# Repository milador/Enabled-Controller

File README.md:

# Enabled Controller

Enabled Controller Wireless is an open-source switch interface that enables those with limited or no hand movement to be able to use Adaptive switches and analog joysticks as inputs to operate their computers, smartphones, and game consoles.

The device offers up to eight switch input enclosures through eight 3.5mm audio jacks and four analog inputs through two 3.5mm headphone jacks. The two 3.5mm headphone jacks can be used to connect up to two X-Y analog joysticks.

The internal RGB led of ItsyBitsy and external NeoPixel is used to provide visual feedback for each action.

## Assembly Instructions Manual

The <a href="https://github.com/milador/Enabled-Controller/blob/master/Documentation/Build_Manuals/Enabled_Controller_Instructions_Manual.pdf">Assembly Instructions Manual</a> is available to download.

## User Manual

### Enabled Controller USB User Manual

<a href="https://github.com/milador/Enabled-Controller/blob/master/Documentation/User_Manuals/Enabled_Controller_USB_User_Manual.pdf">Enabled_Controller_USB_User_Manual.pdf</a>

### Enabled Controller Joystick User Manual 

<a href="https://github.com/milador/Enabled-Controller/blob/master/Documentation/User_Manuals/Enabled_Controller_Joystick_User_Manual.pdf">Enabled_Controller_Joystick_User_Manual.pdf</a>

## Parts

The <a href="https://github.com/milador/Enabled-Controller/blob/master/Components/Enabled_Controller_BOM.csv">BOM</a> file is available to download.

## Software

### Enabled_Controller_USB_Software.ino  

The <a href="https://raw.githubusercontent.com/milador/Enabled-Controller/master/Software/Arduino/Enabled_Controller_USB_Software/Enabled_Controller_USB_Software.ino">Enabled_Controller_USB_Software.ino</a> allows you to use adaptive switches as input method via keyboard/mouse HID profiles. 

### Enabled_Controller_Joystick_Software.ino  

The <a href="https://raw.githubusercontent.com/milador/Enabled-Controller/master/Software/Arduino/Enabled_Controller_Joystick_Software/Enabled_Controller_Joystick_Software.ino">Enabled_Controller_Joystick_Software.ino</a> allows you to use adaptive switches as input method via joystick HID profiles. 

## Hardware 

### PCB Design 

The <a href="https://github.com/milador/Enabled-Controller/tree/master/Hardware/PCB">PCB files</a> including both PCB Eagle design files and generated gerber files are available to download.

Front PCB:

Back PCB:

Assembled:

Assembly Animation:

https://www.youtube.com/watch?v=7AMCL-cITrQ

### Enclosure

The <a href="https://github.com/milador/Enabled-Controller/tree/master/Hardware/Enclosure">Enclosure files</a> including both STL and STEP enclosure files are available to download.

## License

### Creative Commons Attribution-NonCommercial-ShareAlike (CC-BY-NC-SA)

Copyright (c) 2020 Milador

A creative commons license that bans commercial use and requires you to release any modified works under this license.

<br />This work is licensed under a <a rel="license" href="http://creativecommons.org/licenses/by-nc-sa/3.0/">Creative Commons Attribution-NonCommercial-ShareAlike 3.0 Unported License</a>.

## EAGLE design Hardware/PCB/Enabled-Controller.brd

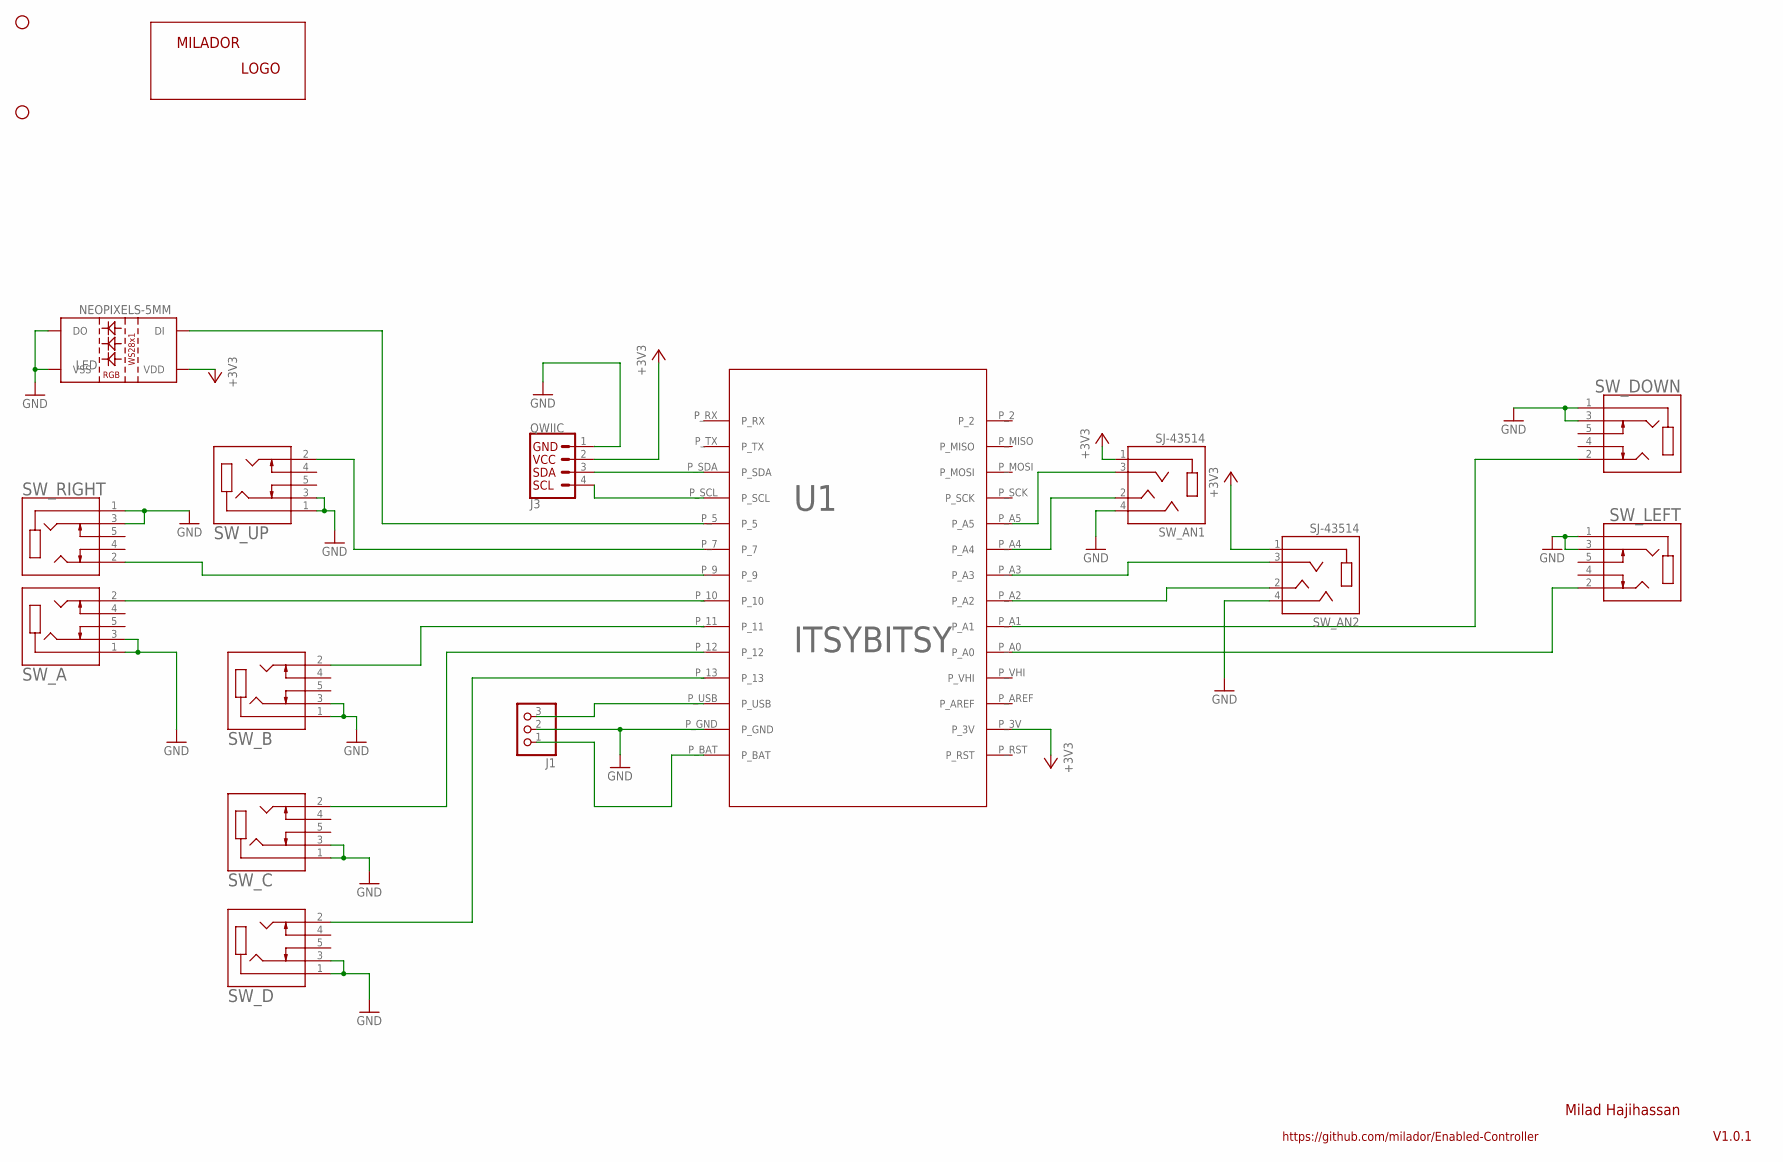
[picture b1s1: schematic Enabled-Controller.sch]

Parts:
J1: HEADER_FEMALE-1X3-LONGER; HEADER_FEMALE-1X03_LONGER
J3: QWIIC; CONNECTORS_JST04_1MM_RA
LABEL1: MILADOR-LOGO-; MILADOR_LOGO1
LED: NEOPIXELS-5MM
STANDOFF1, STANDOFF2: STAND-OFF-; STAND-OFF
SW_A: CUI_SJ1-3535NGSJ1-3535NG; CUI_SJ1-3535NG
SW_AN1, SW_AN2: SJ-43514; CUI_SJ-43514
SW_B: CUI_SJ1-3535NGSJ1-3535NG; CUI_SJ1-3535NG
SW_C: CUI_SJ1-3535NGSJ1-3535NG; CUI_SJ1-3535NG
SW_D: CUI_SJ1-3535NGSJ1-3535NG; CUI_SJ1-3535NG
SW_DOWN: CUI_SJ1-3535NGSJ1-3535NG; CUI_SJ1-3535NG
SW_LEFT: CUI_SJ1-3535NGSJ1-3535NG; CUI_SJ1-3535NG
SW_RIGHT: CUI_SJ1-3535NGSJ1-3535NG; CUI_SJ1-3535NG
SW_UP: CUI_SJ1-3535NGSJ1-3535NG; CUI_SJ1-3535NG
U1: ITSYBITSY; ITSYBITSY-V2

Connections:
+3V3: J3.2, LED.P2 (VDD), SW_AN1.1 (SLEEVE), SW_AN2.1 (SLEEVE), U1.P_3V
GND: J1.2, J3.1, LED.P3 (VSS), LED.P4 (DO), SW_A.1, SW_A.3, SW_AN1.4 (RING2), SW_AN2.4 (RING2), SW_B.1, SW_B.3, SW_C.1, SW_C.3, SW_D.1, SW_D.3, SW_DOWN.1, SW_DOWN.3, SW_LEFT.1, SW_LEFT.3, SW_RIGHT.1, SW_RIGHT.3, SW_UP.1, SW_UP.3, U1.P_GND
unnamed: SW_D.2, U1.P_13
unnamed: SW_C.2, U1.P_12
unnamed: SW_B.2, U1.P_11
unnamed: SW_AN1.2 (TIP), U1.P_A4
unnamed: SW_DOWN.2, U1.P_A1
unnamed: SW_RIGHT.2, U1.P_9
unnamed: SW_UP.2, U1.P_7
unnamed: SW_AN1.3 (RING1), U1.P_A5
unnamed: SW_AN2.3 (RING1), U1.P_A3
unnamed: SW_A.2, U1.P_10
unnamed: SW_LEFT.2, U1.P_A0
unnamed: SW_AN2.2 (TIP), U1.P_A2
unnamed: LED.P1 (DI), U1.P_5
unnamed: J3.4, U1.P_SCL
unnamed: J3.3, U1.P_SDA
unnamed: J1.3, U1.P_USB
unnamed: J1.1, U1.P_BAT

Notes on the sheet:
V1.0.1
Milad Hajihassan
https://github.com/milador/Enabled-Controller

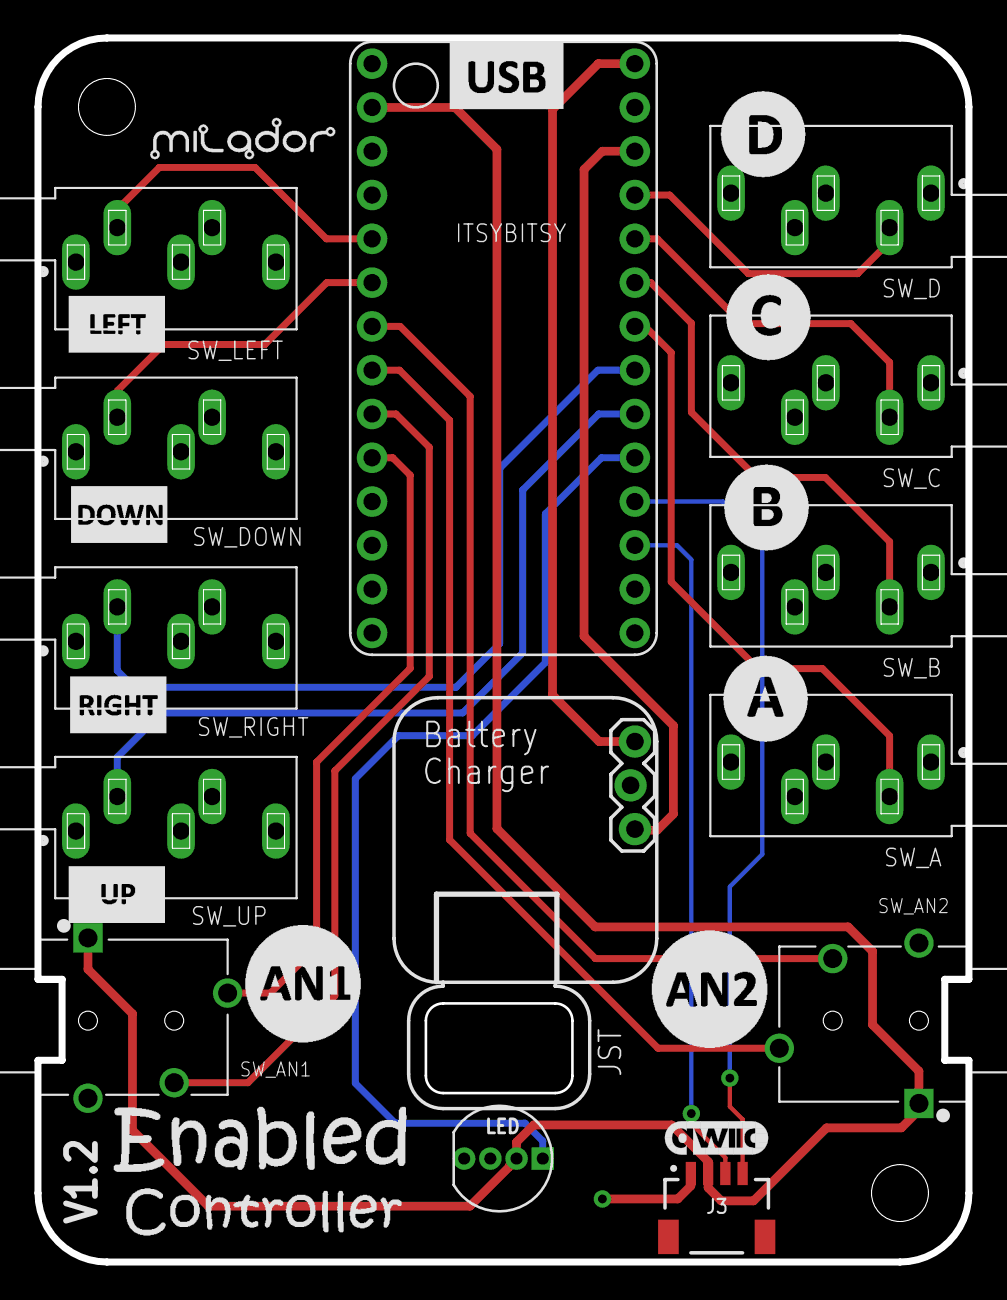
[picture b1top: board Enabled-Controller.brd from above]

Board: 2 copper layers, 54.0 x 71.0 mm, 18 parts (0 on the bottom side), 19 nets.

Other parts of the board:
LABEL2: QWIIC_6MM

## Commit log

2020-10-01 Added components list
2020-10-01 Added PCB files
2020-10-01 Added experimental software
2020-10-01 Added pictures
2020-10-01 Updated readme file
2020-11-29 Added enclosure files
2020-11-29 Updated Enclosure files for easy print
2020-12-20 Updated BOM and added M2.5 screws
2020-12-20 Redesigned the enclosure ( Snap fit )
2020-12-23 Updated BOM for two versions
2020-12-23 Added Instructions manual version 1.0
2020-12-23 Updated software naming convention
2020-12-26 Updated manual
2020-12-26 Updated the USB Software
2020-12-26 Waiting for Joystick API
2020-12-26 Waiting for BT joystick API
2021-01-12 Updated enclosure files
2021-01-17 Updated Enclosure : Snap wall height was increased by 0.8mm.
2021-01-18 Updated BOM file : Price updated and changed screw part
2021-01-18 Added the Assembly Instructions Manual
2021-01-18 Added PCB gerber files
2021-01-18 Updated Images
2021-01-18 Moved the arduino code to new directory
2021-01-18 Updated the manual : Updated software link
2021-01-18 Updated information
2021-01-18 Updated readme : Corrected links
2021-01-21 USB Switch and joystick code added
2021-01-21 Updated Software : Fixed LED code and added more switch options
2021-01-21 Updated instructions
2021-01-21 Updated user manual title
2021-01-21 Added user manuals
2021-01-21 Added software and user manual links to readme
2021-01-25 Added Joystick Assembly
2021-01-25 Updated tables and instructions based on software change ( e,f,g,h keys to UP, RIGHT, DOWN,LEFT Keys)
2021-01-25 Updated switch key codes and added OS Profile selection option ( e,f,g,h keys to UP, RIGHT, DOWN,LEFT Keys)
2021-01-31 Updated Assembly manual 1.11
2021-02-01 Corrected links
2021-02-26 Added license
2021-02-26 Update LICENSE
2021-04-10 Updated joystick user manual
2021-05-07 Removed old wireless code
2021-05-22 Added wireless version of Enabled Controller and added mouse mode
2021-06-07 Updated Eagle files
2021-08-29 Added low power mode to wireless code
2021-08-29 Added updated PCB files
2021-08-29 Updated enclosure for version 1.2
2021-08-29 Updated BOM Files
2021-08-29 Updated enclosure battery holder
2021-10-01 Updated all files to version 1.2
2021-10-04 Updated the instructions manual
2023-05-27 Added mouse mover code
2023-06-02 Mouse mover software bugs resolved
2023-06-02 Added mouse mover software

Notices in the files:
parts and their libraries:
SparkFun-Aesthetics: Licensing: Creative Commons ShareAlike 4.0 International - https://creativecommons.org/licenses/by-sa/4.0
